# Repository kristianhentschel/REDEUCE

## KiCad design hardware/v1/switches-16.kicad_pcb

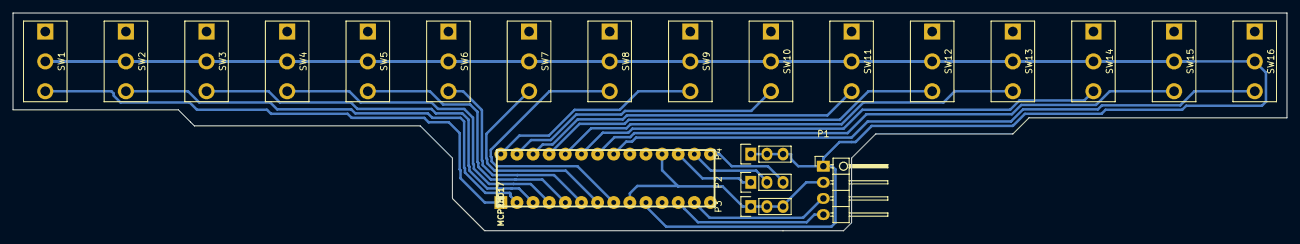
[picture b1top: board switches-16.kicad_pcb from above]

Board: 2 copper layers, 200.7 x 34.3 mm, 21 parts (0 on the bottom side), 23 nets.

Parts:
P1: CONN_01X04; Pin_Header_Angled_1x04
P2, P3, P4: CONN_01X03; Pin_Header_Straight_1x03
SW1, SW2, SW3, SW4, SW5, SW6, SW7, SW8, SW9, SW10, SW11, SW12, SW13, SW14, SW15, SW16: SWITCH_INV; SW_SPDT-custom
U1: MCP23017; DIL28

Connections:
/SCK: P1.4, U1.12
/SDA: P1.3, U1.13
GND: P1.1, P4.1, P4.2, P4.3, SW1.2, SW2.2, SW3.2, SW4.2, SW5.2, SW6.2, SW7.2, SW8.2, SW9.2, SW10.2, SW11.2, SW12.2, SW13.2, SW14.2, SW15.2, SW16.2, U1.10
unnamed: P2.1, U1.17
unnamed: P2.2, U1.16
unnamed: P2.3, U1.15
unnamed: SW1.3, U1.1
unnamed: SW2.3, U1.2
unnamed: SW3.3, U1.3
unnamed: SW4.3, U1.4
unnamed: SW5.3, U1.5
unnamed: SW6.3, U1.6
unnamed: SW7.3, U1.7
unnamed: SW8.3, U1.8
unnamed: SW9.3, U1.28
unnamed: SW10.3, U1.27
unnamed: SW11.3, U1.26
unnamed: SW12.3, U1.25
unnamed: SW13.3, U1.24
unnamed: SW14.3, U1.23
unnamed: SW15.3, U1.22
unnamed: SW16.3, U1.21
VDD: P1.2, P3.1, P3.2, P3.3, U1.9, U1.18

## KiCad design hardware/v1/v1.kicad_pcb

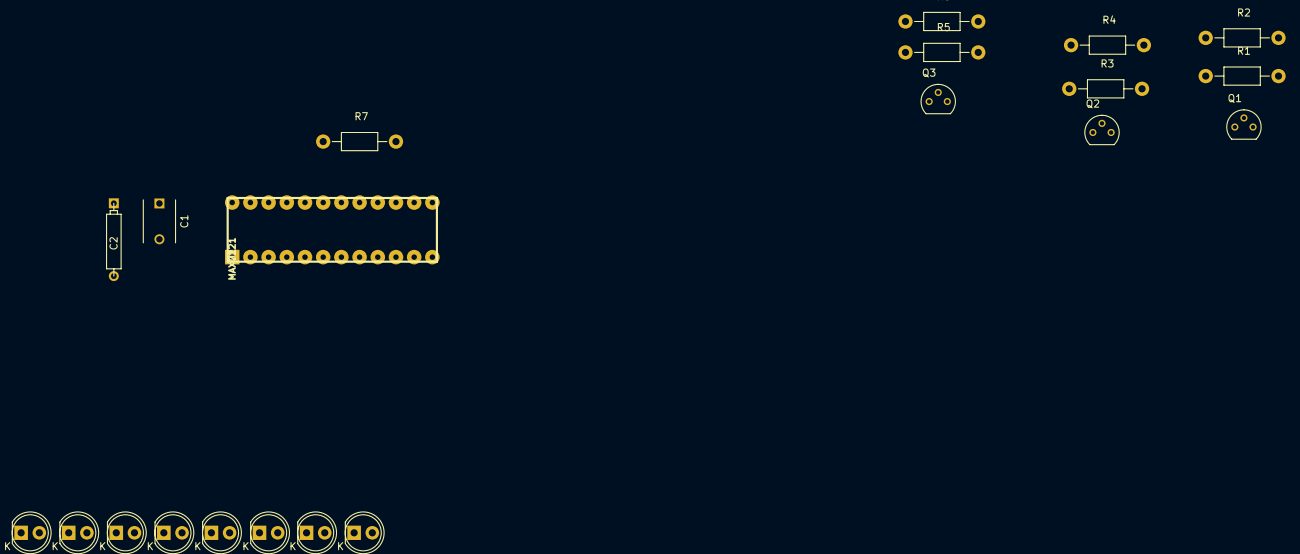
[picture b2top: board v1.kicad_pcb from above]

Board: 2 copper layers, 21 parts (0 on the bottom side), 21 nets, no tracks yet.

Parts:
C1: C; C_Disc_D6_P5
C2: CP; CP4
D1, D2, D3, D4, D5, D6, D7, D8: LED; LED-5MM
Q1, Q2, Q3: 2N7000; TO-92_Molded_Narrow
R1, R2, R3, R4, R5, R6: 10K; Resistor_Horizontal_RM10mm
R7: R_SET; Resistor_Horizontal_RM10mm
U1: MAX7221; DIL24

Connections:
/ledcontroller/DIG0: D1.1, D2.1, D3.1, D4.1, D5.1, D6.1, D7.1, D8.1, U1.2
/ledcontroller/GND: C1.2, C2.2, U1.4, U1.9
/ledcontroller/VCC: C1.1, C2.1, R7.1, U1.19
/ledrow/LED0: D1.2, U1.14
/ledrow/LED1: D2.2, U1.16
/ledrow/LED2: D3.2, U1.20
/ledrow/LED3: D4.2, U1.23
/ledrow/LED4: D5.2, U1.21
/ledrow/LED5: D6.2, U1.15
/ledrow/LED6: D7.2, U1.17
/ledrow/LED7: D8.2, U1.22
/piconnect/sheet57A33FA6/3V3: Q1.2, R1.1
/piconnect/sheet57A33FA6/CMOS_OUT: Q1.1, R2.2
/piconnect/sheet57A33FA6/TTL_IN: Q1.3, R1.2
/piconnect/sheet57A33FA7/3V3: Q2.2, R3.1
/piconnect/sheet57A33FA7/CMOS_OUT: Q2.1, R4.2
/piconnect/sheet57A33FA7/TTL_IN: Q2.3, R3.2
/piconnect/sheet57A33FA8/3V3: Q3.2, R5.1
/piconnect/sheet57A33FA8/CMOS_OUT: Q3.1, R6.2
/piconnect/sheet57A33FA8/TTL_IN: Q3.3, R5.2
unnamed: R7.2, U1.18
